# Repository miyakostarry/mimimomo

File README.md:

#mimimomo

Mimimomo is a flower-shaped MIDI controller PCB designed using KiCad. The project combines capacitive touch pads, mechanical switches, slide potentiometers, a rotary encoder, and RGB LEDs to create a custom music controller.
basically i had vission but it didn't turned out the way i wanted because i struggled alot when placing all the parts and also while making the capacitive touch footprints like i was confused it took alot of time to figure out how the things will work anyway i still love it becayse i completed it gonna add more doodles and make it freaky!@! and doodlie╰(*°▽°*)╯
THANKS!!

##Schematic

## Components Used

| Component                      | Quantity | Purpose                                                               |
| ------------------------------ | -------: | --------------------------------------------------------------------- |
| Waveshare ESP32-S3-Zero        |        1 | Microcontroller for processing inputs and handling MIDI communication |
| Capacitive touch pads          |        6 | Touch-based controls                                                  |
| SK6812 MINI-E RGB LEDs         |        6 | Lighting and visual feedback                                          |
| Bourns slide potentiometers    |        2 | Adjustable controls for parameters such as volume or effects          |
| EC11 rotary encoder            |        1 | Rotary input for adjusting values                                     |
| Kailh Choc mechanical switches |        4 | Physical button inputs                                                |

## Tools Used

* KiCad — PCB layout and schematic design
* Git — Version control
* GitHub — Project hosting and version management

## Work Completed

* Designed a flower-shaped PCB layout in KiCad.
* Created a custom hexagonal copper footprint for the touch pads.
* Added and positioned the components on the PCB.
* Arranged the components to fit the flower-shaped design.
* Explored routing connections across the front and back copper layers.
* Planned the placement of RGB LEDs on the back of the PCB.
* Uploaded the KiCad project files and custom touch-pad footprint to GitHub.

## Repository Structure

* `mimi-kicad/` — KiCad project files, including the schematic and PCB layout.
* `touch_padd.pretty/` — Custom capacitive touch-pad footprint library.

## MADE FOR HACKCLUB HALF-LIFE

This project is a learning experience in PCB design, electronics, and building a custom MIDI controller from scratch.

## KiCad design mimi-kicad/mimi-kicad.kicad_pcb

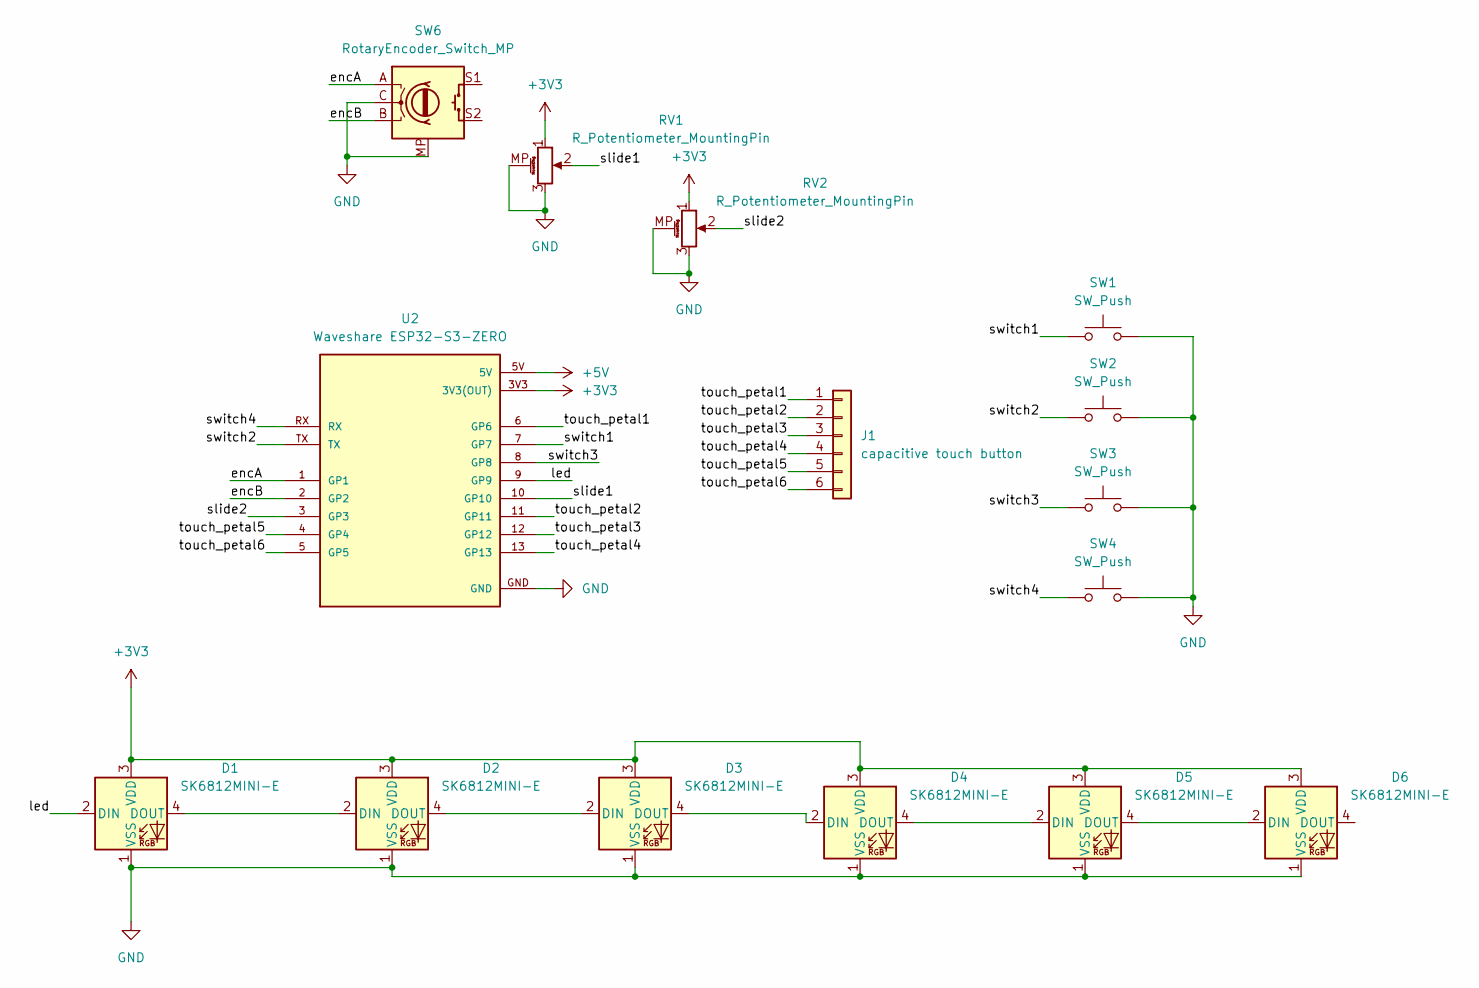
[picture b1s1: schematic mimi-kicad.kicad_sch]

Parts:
D1, D2, D3, D4, D5, D6: SK6812MINI-E; LED_SK6812MINI-E_3.2x2.8mm_P1.5mm_ReverseMount
J1: capacitive touch button; touch_Paddd
RV1, RV2: R_Potentiometer_MountingPin; Potentiometer_Bourns_PTA1543_Single_Slide
SW1, SW2, SW3, SW4: SW_Push; Kailh Choc Low-Profile Switches
SW6: RotaryEncoder_Switch_MP; RotaryEncoder_Alps_EC11E-Switch_Vertical_H20mm
U2: Waveshare ESP32-S3-ZERO; Waveshare ESP32-S3-Zero; PARTREV NA

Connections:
+3V3: D1.3 (VDD), D2.3 (VDD), D3.3 (VDD), D4.3 (VDD), D5.3 (VDD), D6.3 (VDD), RV1.1, RV2.1, U2.3V3 (3V3(OUT))
+5V: U2.5V
/encA: SW6.A, U2.1 (GP1)
/encB: SW6.B, U2.2 (GP2)
/led: D1.2 (DIN), U2.9 (GP9)
/slide1: RV1.2, U2.10 (GP10)
/slide2: RV2.2, U2.3 (GP3)
/switch1: SW1.1, U2.7 (GP7)
/switch2: SW2.1, U2.TX
/switch3: SW3.1, U2.8 (GP8)
/switch4: SW4.1, U2.RX
/touch_petal1: J1.1, U2.6 (GP6)
/touch_petal2: J1.2, U2.11 (GP11)
/touch_petal3: J1.3, U2.12 (GP12)
/touch_petal4: J1.4, U2.13 (GP13)
/touch_petal5: J1.5, U2.4 (GP4)
/touch_petal6: J1.6, U2.5 (GP5)
GND: D1.1 (VSS), D2.1 (VSS), D3.1 (VSS), D4.1 (VSS), D5.1 (VSS), D6.1 (VSS), RV1.3, RV1.MP (MountPin), RV2.3, RV2.MP (MountPin), SW1.2, SW2.2, SW3.2, SW4.2, SW6.C, SW6.MP, U2.GND
unnamed: D1.4 (DOUT), D2.2 (DIN)
unnamed: D2.4 (DOUT), D3.2 (DIN)
unnamed: D3.4 (DOUT), D4.2 (DIN)
unnamed: D4.4 (DOUT), D5.2 (DIN)
unnamed: D5.4 (DOUT), D6.2 (DIN)

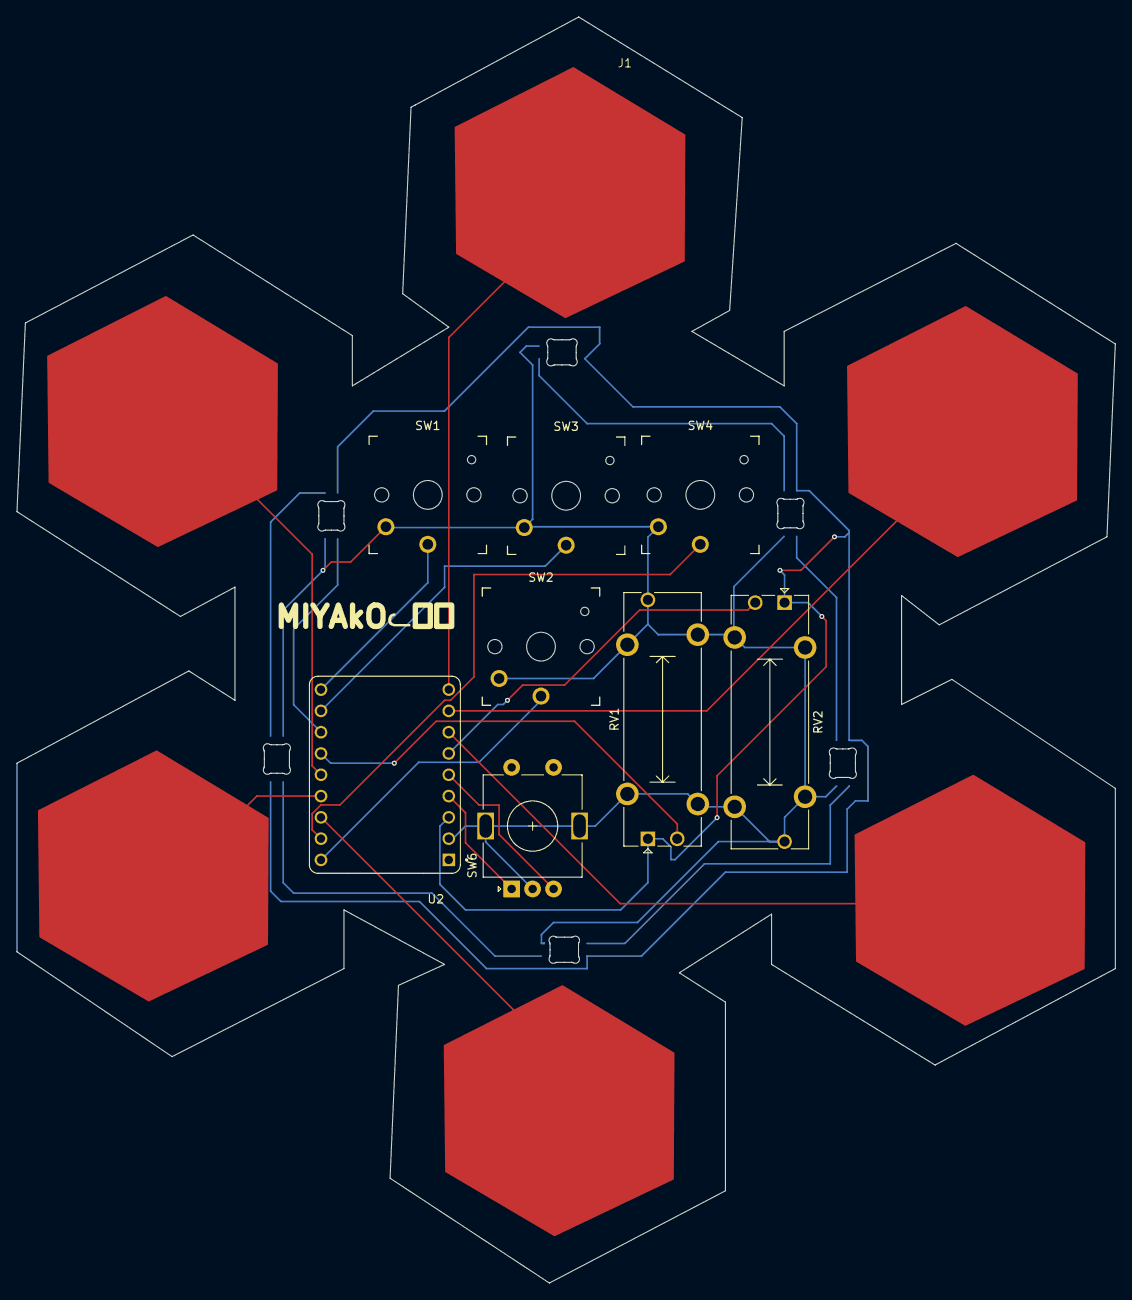
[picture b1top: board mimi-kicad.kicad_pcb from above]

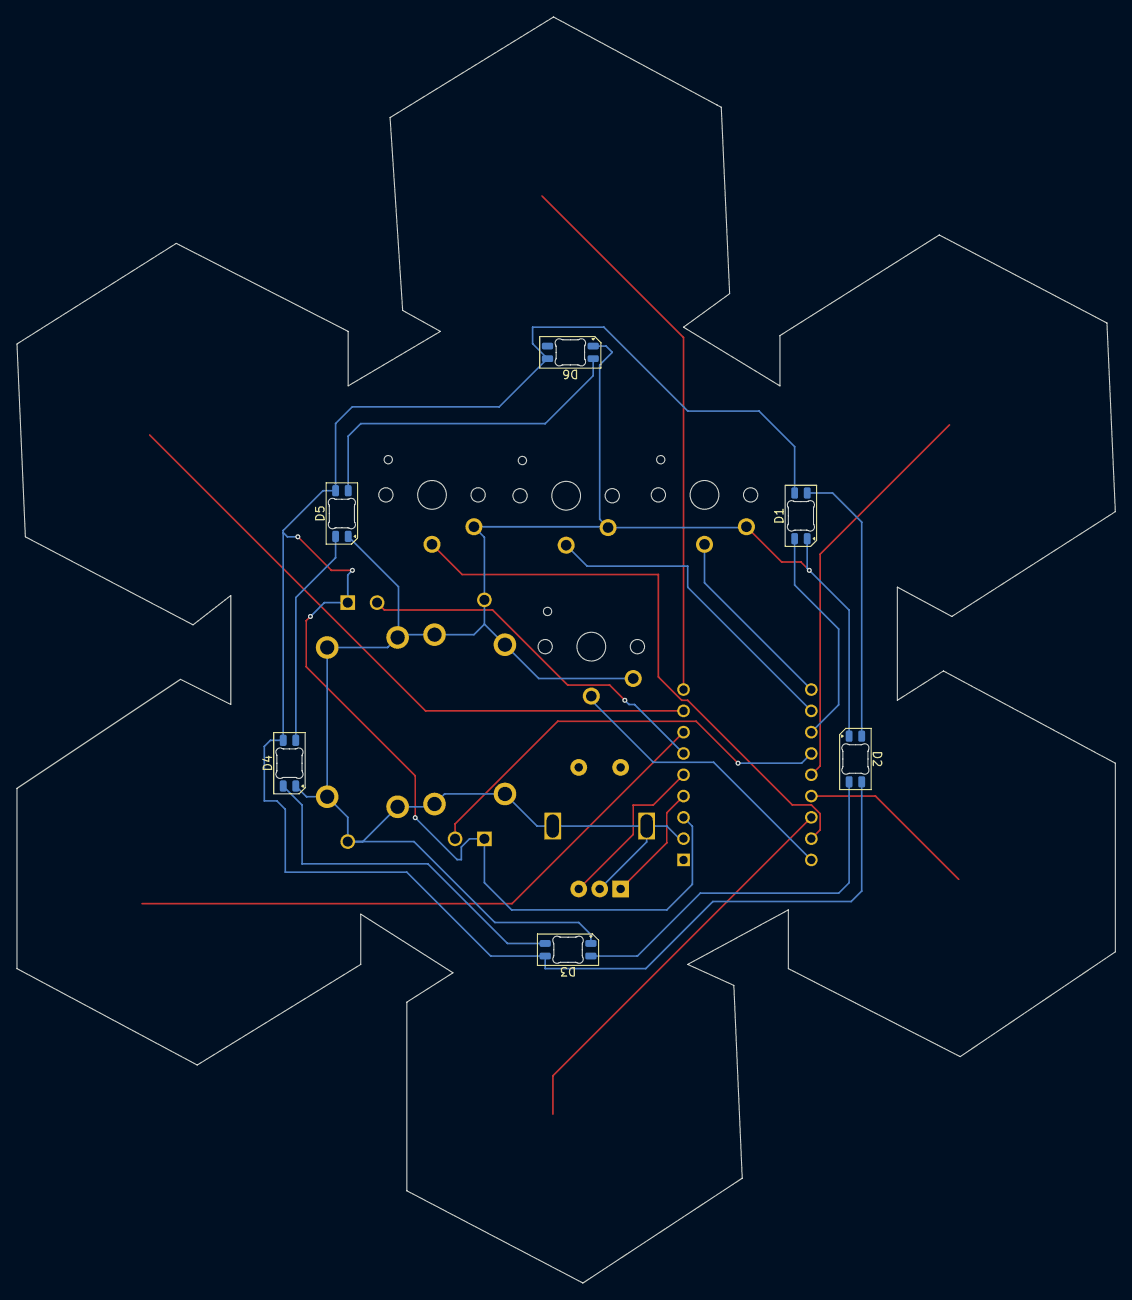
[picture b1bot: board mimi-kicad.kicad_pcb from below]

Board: 2 copper layers, 131.0 x 151.0 mm, 15 parts (6 on the bottom side), 22 nets.
